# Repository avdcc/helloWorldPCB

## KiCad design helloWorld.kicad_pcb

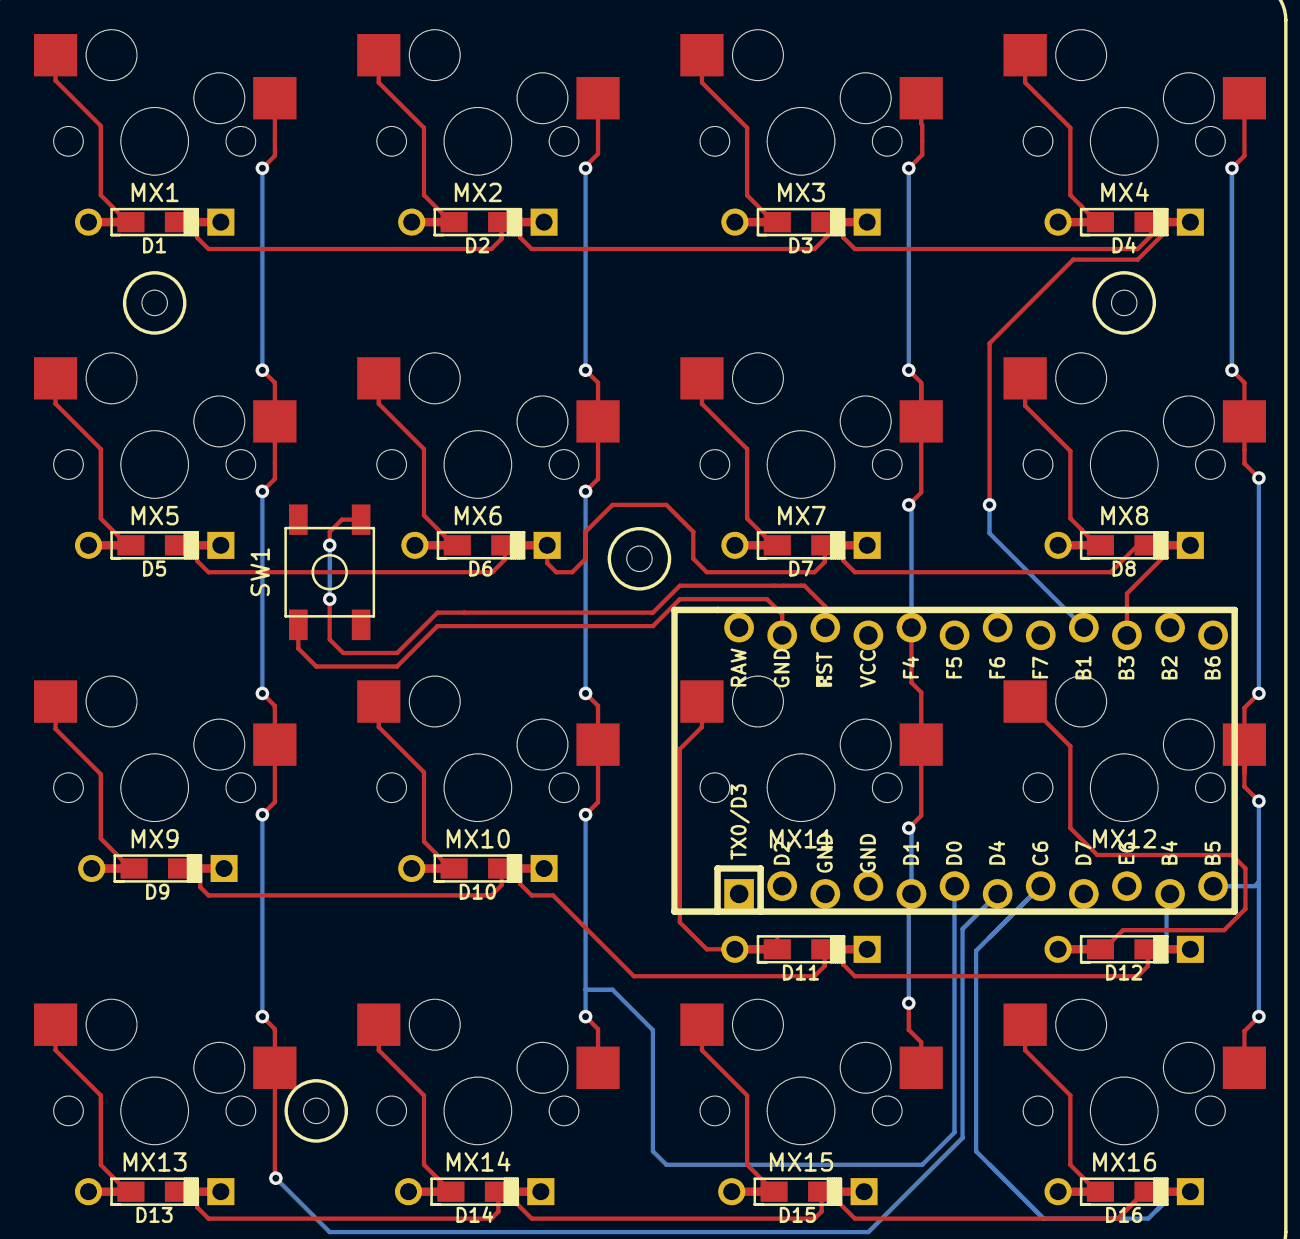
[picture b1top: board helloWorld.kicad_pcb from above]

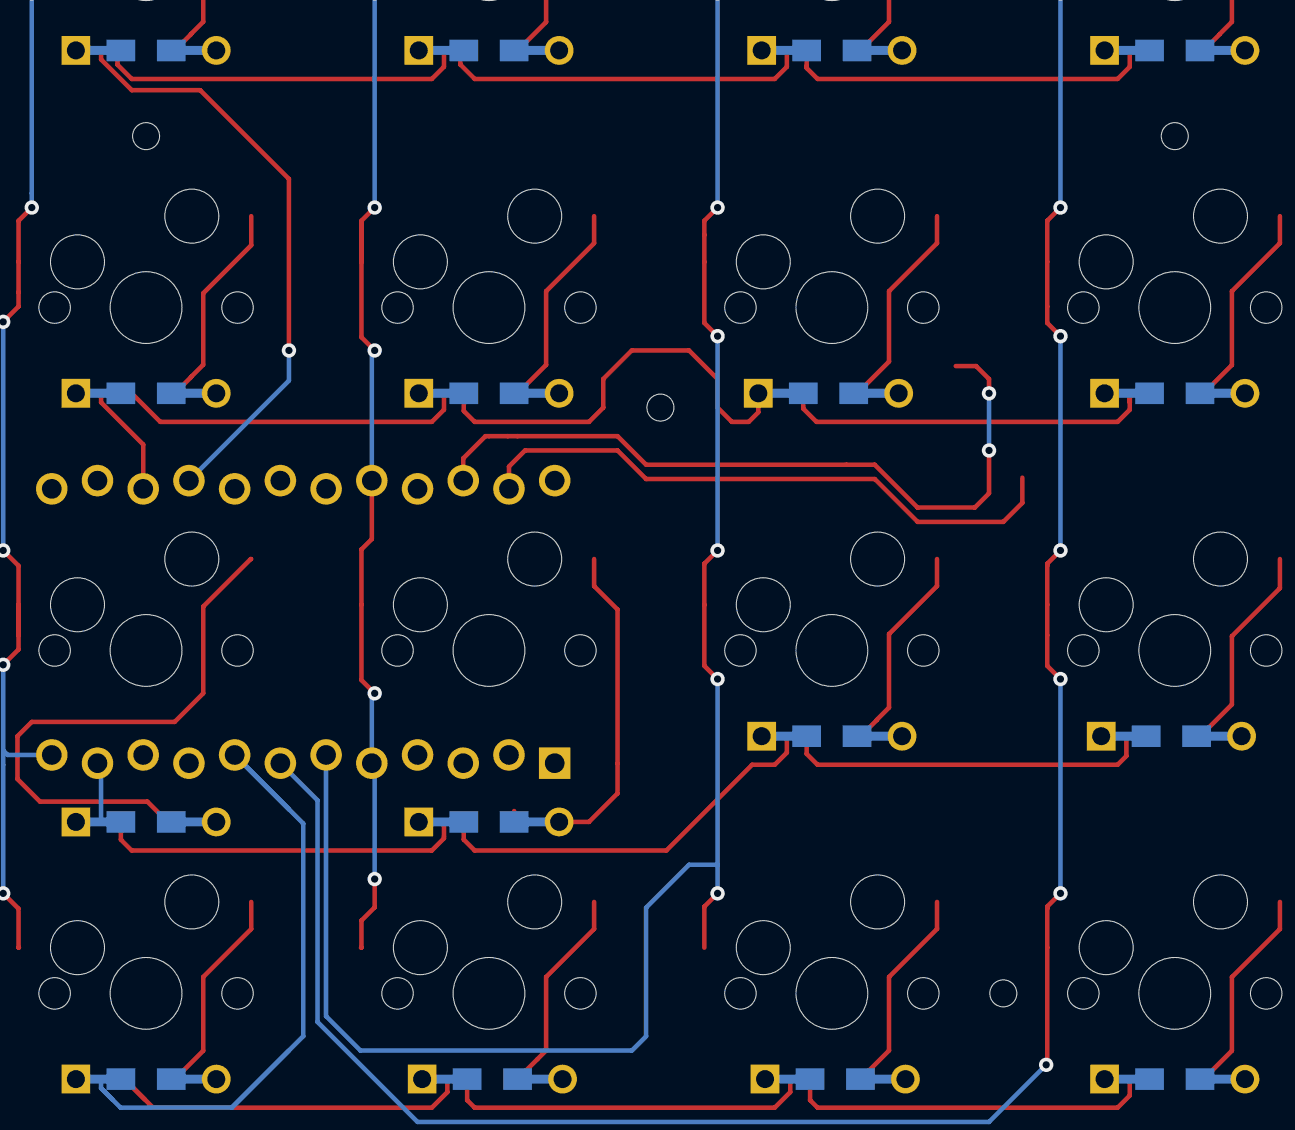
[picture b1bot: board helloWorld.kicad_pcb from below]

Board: 2 copper layers, 34 parts (16 on the bottom side), 26 nets.

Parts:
D1, D2, D3, D4, D5, D6, D7, D8, D9, D10, D11, D12, D13, D14, D15, D16: D_Small; Diode-dual
MX1, MX2, MX3, MX4, MX5, MX6, MX7, MX8, MX9, MX10, MX11, MX12, MX13, MX14, MX15, MX16: MX-1U; MXOnly-1U-Hotswap
SW1: SW_Push; SKQG-1155865
U1: ProMicro; ArduinoProMicro-ZigZagSide

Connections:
COL0: MX1.1, MX5.1, MX9.1, MX13.1, U1.7
COL1: MX2.1, MX6.1, MX10.1, MX14.1, U1.6
COL2: MX3.1, MX7.1, MX11.1, MX15.1, U1.5, U1.20
COL3: MX4.1, MX8.1, MX12.1, MX16.1, U1.12
unnamed: D1.2, MX1.2
unnamed: D2.2, MX2.2
unnamed: D3.2, MX3.2
unnamed: D4.2, MX4.2
unnamed: D5.2, MX5.2
unnamed: D6.2, MX6.2
unnamed: D7.2, MX7.2
unnamed: D8.2, MX8.2
unnamed: D9.2, MX9.2
unnamed: D10.2, MX10.2
unnamed: D11.2, MX11.2
unnamed: D12.2, MX12.2
unnamed: D13.2, MX13.2
unnamed: D14.2, MX14.2
unnamed: D15.2, MX15.2
unnamed: D16.2, MX16.2
unnamed: SW1.1, U1.23
unnamed: SW1.2, U1.22
ROW0: D1.1, D2.1, D3.1, D4.1, U1.16
ROW1: D5.1, D6.1, D7.1, D8.1, U1.15
ROW2: D9.1, D10.1, D11.1, D12.1, U1.11
ROW3: D13.1, D14.1, D15.1, D16.1, U1.8
